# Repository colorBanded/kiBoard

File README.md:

# kiBoard
Full 104-key Keyboard designed as a submission for the **2026 Hackclub Stardance/Outpost Event**, created using KiCAD and Fusion 360. Uses the QMK firmware for ease of use and modularity.

## Features
* Raspberry Pi Pico based microcontroller
* 160 Keys
* Second function row + built in macro pad

## Layout

## Enclosure

-- I made the enclosure screwless so that you could nudge the top on for easier access to the internal board. (feel free to mess with it)

## BOM
| Reference | Qty | Value | Footprint | Datasheet |
|-----------|-----|-------|-----------|-----------|
| A1 | 1 | RaspberryPi_Pico | Module:RaspberryPi_Pico_Common_Unspecified | https://datasheets.raspberrypi.com/pico/pico-datasheet.pdf |
| D1–D158 | 158 | 1N4148 | Diode_THT:D_DO-35_SOD27_P7.62mm_Horizontal | https://assets.nexperia.com/documents/data-sheet/1N4148_1N4448.pdf |
| SW1–SW158 | 158 | SW_Push_45deg | Button_Switch_Keyboard:SW_Cherry_MX_1.00u_PCB | |
| SW159 | 1 | SW_Push | Button_Switch_Keyboard:SW_Cherry_MX_1.00u_PCB | |
| U1 | 1 | PCF8574AP | Package_DIP:DIP-16_W7.62mm | https://www.nxp.com/docs/en/data-sheet/PCF8574_PCF8574A.pdf |

Note: You can use any extended regular keyboard keycap set but it will need extra standard 1.0u keycaps for the remaining keys.

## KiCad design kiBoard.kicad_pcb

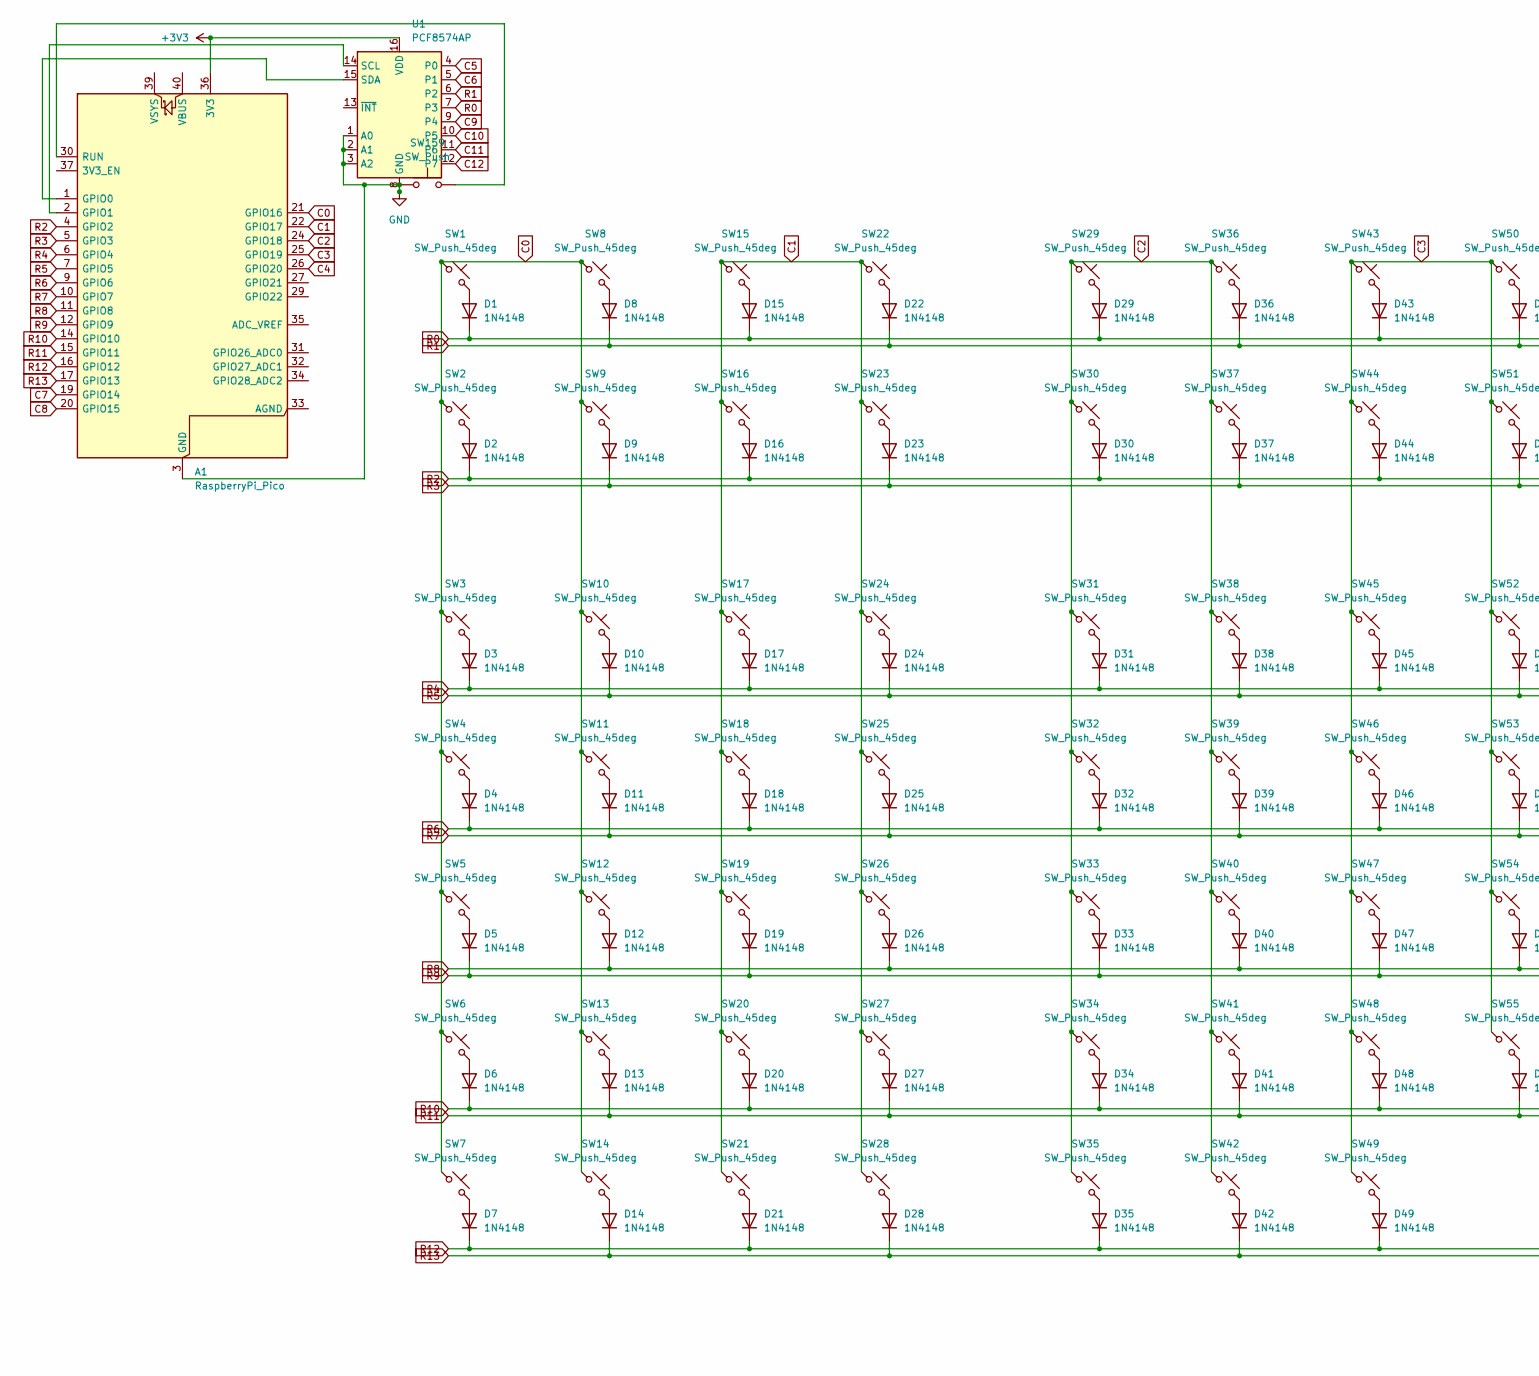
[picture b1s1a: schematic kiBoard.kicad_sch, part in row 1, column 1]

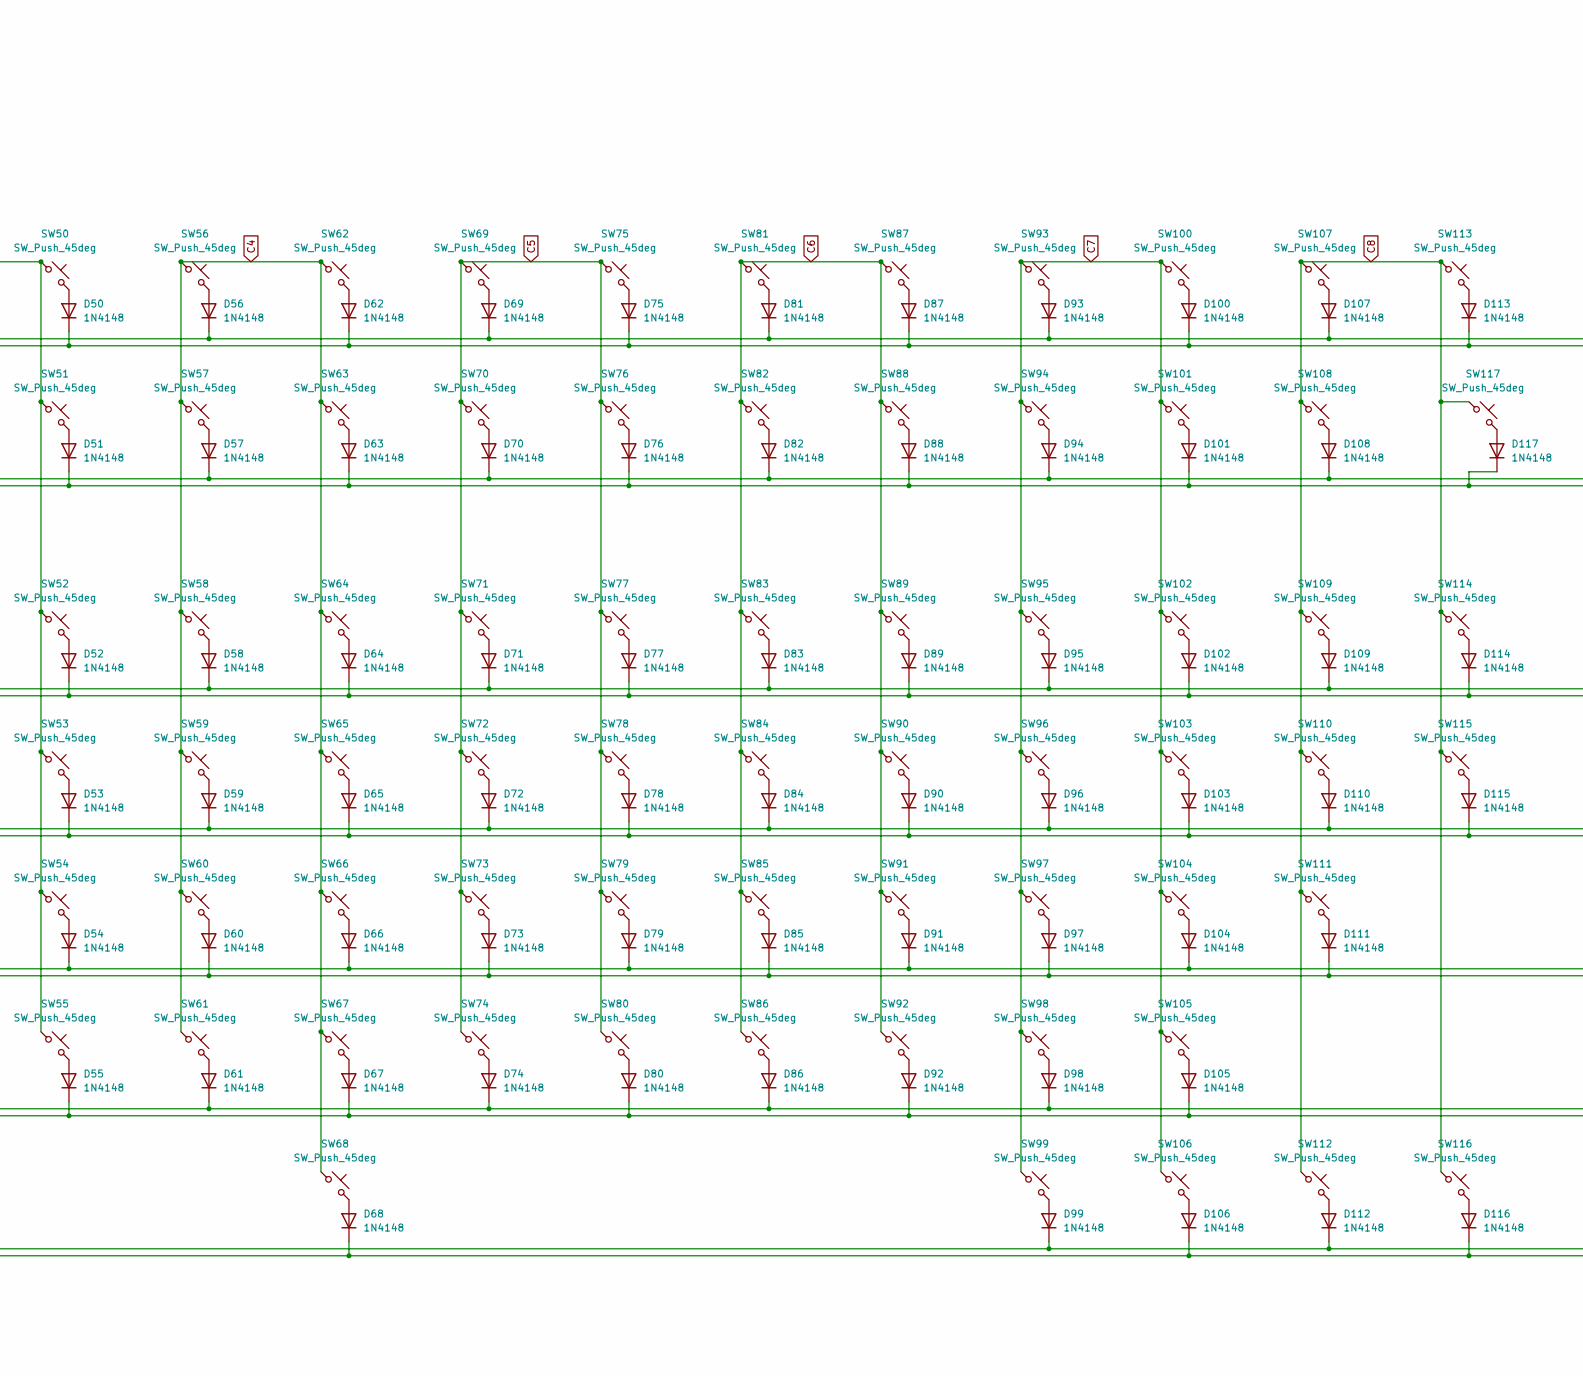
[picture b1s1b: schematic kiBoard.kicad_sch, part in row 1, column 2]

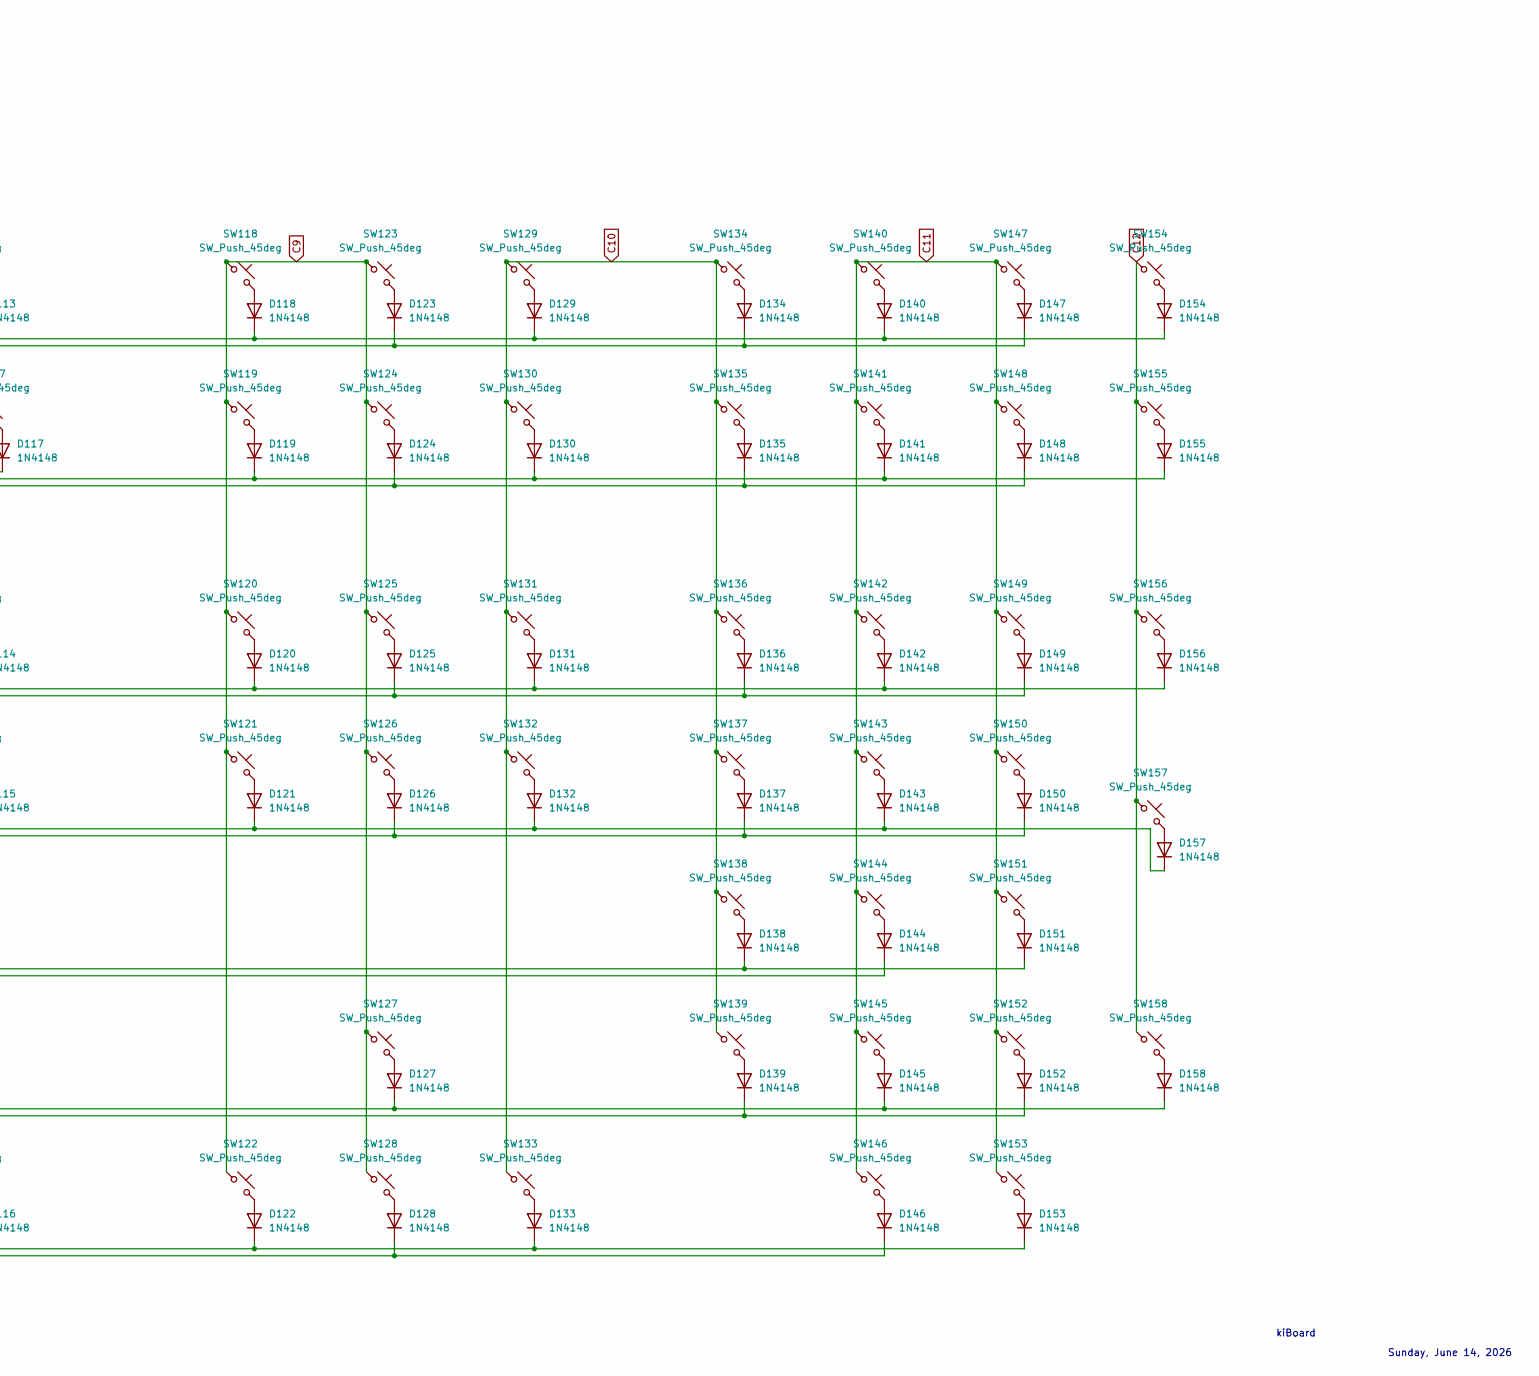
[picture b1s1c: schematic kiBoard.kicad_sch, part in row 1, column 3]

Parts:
A1: RaspberryPi_Pico; RaspberryPi_Pico_Common_Unspecified
D1, D2, D3, D4, D5, D6, D7, D8, D9, D10, D11, D12, D13, D14, D15, D16, D17, D18, D19, D20, D21, D22, D23, D24, D25, D26, D27, D28, D29, D30, D31, D32, D33, D34, D35, D36, D37, D38, D39, D40, D41, D42, D43, D44, D45, D46, D47, D48, D49, D50, D51, D52, D53, D54, D55, D56, D57, D58, D59, D60, D61, D62, D63, D64, D65, D66, D67, D68, D69, D70, D71, D72, D73, D74, D75, D76, D77, D78, D79, D80, D81, D82, D83, D84, D85, D86, D87, D88, D89, D90, D91, D92, D93, D94, D95, D96, D97, D98, D99, D100, D101, D102, D103, D104, D105, D106, D107, D108, D109, D110, D111, D112, D113, D114, D115, D116, D117, D118, D119, D120, D121, D122, D123, D124, D125, D126, D127, D128, D129, D130, D131, D132, D133, D134, D135, D136, D137, D138, D139, D140, D141, D142, D143, D144, D145, D146, D147, D148, D149, D150, D151, D152, D153, D154, D155, D156, D157, D158: 1N4148; D_DO-35_SOD27_P7.62mm_Horizontal
SW1, SW2, SW3, SW4, SW5, SW6, SW7, SW8, SW9, SW10, SW11, SW12, SW13, SW14, SW15, SW16, SW17, SW18, SW19, SW20, SW21, SW22, SW23, SW24, SW25, SW26, SW27, SW28, SW29, SW30, SW31, SW32, SW33, SW34, SW35, SW36, SW37, SW38, SW39, SW40, SW41, SW42, SW43, SW44, SW45, SW46, SW47, SW48, SW49, SW50, SW51, SW52, SW53, SW54, SW55, SW56, SW57, SW58, SW59, SW60, SW61, SW62, SW63, SW64, SW65, SW66, SW67, SW68, SW69, SW70, SW71, SW72, SW73, SW74, SW75, SW76, SW77, SW78, SW79, SW80, SW81, SW82, SW83, SW84, SW85, SW86, SW87, SW88, SW89, SW90, SW91, SW92, SW93, SW94, SW95, SW96, SW97, SW98, SW99, SW100, SW101, SW102, SW103, SW104, SW105, SW106, SW107, SW108, SW109, SW110, SW111, SW112, SW113, SW114, SW115, SW116, SW117, SW118, SW119, SW120, SW121, SW122, SW123, SW124, SW125, SW126, SW127, SW128, SW129, SW130, SW131, SW132, SW133, SW134, SW135, SW136, SW137, SW138, SW139, SW140, SW141, SW142, SW143, SW144, SW145, SW146, SW147, SW148, SW149, SW150, SW151, SW152, SW153, SW154, SW155, SW156, SW157, SW158: SW_Push_45deg; SW_Cherry_MX_1.00u_PCB
SW159: SW_Push; SW_Cherry_MX_1.00u_PCB
U1: PCF8574AP; DIP-16_W7.62mm

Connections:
+3V3: A1.36 (3V3), U1.16 (VDD)
C0: A1.21 (GPIO16), SW1.1, SW2.1, SW3.1, SW4.1, SW5.1, SW6.1, SW7.1, SW8.1, SW9.1, SW10.1, SW11.1, SW12.1, SW13.1, SW14.1
C1: A1.22 (GPIO17), SW15.1, SW16.1, SW17.1, SW18.1, SW19.1, SW20.1, SW21.1, SW22.1, SW23.1, SW24.1, SW25.1, SW26.1, SW27.1, SW28.1
C2: A1.24 (GPIO18), SW29.1, SW30.1, SW31.1, SW32.1, SW33.1, SW34.1, SW35.1, SW36.1, SW37.1, SW38.1, SW39.1, SW40.1, SW41.1, SW42.1
C3: A1.25 (GPIO19), SW43.1, SW44.1, SW45.1, SW46.1, SW47.1, SW48.1, SW49.1, SW50.1, SW51.1, SW52.1, SW53.1, SW54.1, SW55.1
C4: A1.26 (GPIO20), SW56.1, SW57.1, SW58.1, SW59.1, SW60.1, SW61.1, SW62.1, SW63.1, SW64.1, SW65.1, SW66.1, SW67.1, SW68.1
C5: SW69.1, SW70.1, SW71.1, SW72.1, SW73.1, SW74.1, SW75.1, SW76.1, SW77.1, SW78.1, SW79.1, SW80.1, U1.4 (P0)
C6: SW81.1, SW82.1, SW83.1, SW84.1, SW85.1, SW86.1, SW87.1, SW88.1, SW89.1, SW90.1, SW91.1, SW92.1, U1.5 (P1)
C7: A1.19 (GPIO14), SW93.1, SW94.1, SW95.1, SW96.1, SW97.1, SW98.1, SW99.1, SW100.1, SW101.1, SW102.1, SW103.1, SW104.1, SW105.1, SW106.1
C8: A1.20 (GPIO15), SW107.1, SW108.1, SW109.1, SW110.1, SW111.1, SW112.1, SW113.1, SW114.1, SW115.1, SW116.1, SW117.1
C9: SW118.1, SW119.1, SW120.1, SW121.1, SW122.1, SW123.1, SW124.1, SW125.1, SW126.1, SW127.1, SW128.1, U1.9 (P4)
C10: SW129.1, SW130.1, SW131.1, SW132.1, SW133.1, SW134.1, SW135.1, SW136.1, SW137.1, SW138.1, SW139.1, U1.10 (P5)
C11: SW140.1, SW141.1, SW142.1, SW143.1, SW144.1, SW145.1, SW146.1, SW147.1, SW148.1, SW149.1, SW150.1, SW151.1, SW152.1, SW153.1, U1.11 (P6)
C12: SW154.1, SW155.1, SW156.1, SW157.1, SW158.1, U1.12 (P7)
GND: A1.3 (GND), A1.8 (GND), A1.13 (GND), A1.18 (GND), A1.23 (GND), A1.28 (GND), A1.38 (GND), SW159.1, U1.1 (A0), U1.2 (A1), U1.3 (A2), U1.8 (GND)
unnamed: A1.1 (GPIO0), U1.15 (SDA)
unnamed: A1.2 (GPIO1), U1.14 (SCL)
unnamed: A1.30 (RUN), SW159.2
unnamed: D1.2 (A), SW1.2
unnamed: D2.2 (A), SW2.2
unnamed: D3.2 (A), SW3.2
unnamed: D4.2 (A), SW4.2
unnamed: D5.2 (A), SW5.2
unnamed: D6.2 (A), SW6.2
unnamed: D7.2 (A), SW7.2
unnamed: D8.2 (A), SW8.2
unnamed: D9.2 (A), SW9.2
unnamed: D10.2 (A), SW10.2
unnamed: D11.2 (A), SW11.2
unnamed: D12.2 (A), SW12.2
unnamed: D13.2 (A), SW13.2
unnamed: D14.2 (A), SW14.2
unnamed: D15.2 (A), SW15.2
unnamed: D16.2 (A), SW16.2
unnamed: D17.2 (A), SW17.2
unnamed: D18.2 (A), SW18.2
unnamed: D19.2 (A), SW19.2
unnamed: D20.2 (A), SW20.2
unnamed: D21.2 (A), SW21.2
unnamed: D22.2 (A), SW22.2
unnamed: D23.2 (A), SW23.2
unnamed: D24.2 (A), SW24.2
unnamed: D25.2 (A), SW25.2
unnamed: D26.2 (A), SW26.2
unnamed: D27.2 (A), SW27.2
unnamed: D28.2 (A), SW28.2
unnamed: D29.2 (A), SW29.2
unnamed: D30.2 (A), SW30.2
unnamed: D31.2 (A), SW31.2
unnamed: D32.2 (A), SW32.2
unnamed: D33.2 (A), SW33.2
unnamed: D34.2 (A), SW34.2
unnamed: D35.2 (A), SW35.2
unnamed: D36.2 (A), SW36.2
unnamed: D37.2 (A), SW37.2
unnamed: D38.2 (A), SW38.2
unnamed: D39.2 (A), SW39.2
unnamed: D40.2 (A), SW40.2
unnamed: D41.2 (A), SW41.2
unnamed: D42.2 (A), SW42.2
unnamed: D43.2 (A), SW43.2
unnamed: D44.2 (A), SW44.2
unnamed: D45.2 (A), SW45.2
unnamed: D46.2 (A), SW46.2
unnamed: D47.2 (A), SW47.2
unnamed: D48.2 (A), SW48.2
unnamed: D49.2 (A), SW49.2
unnamed: D50.2 (A), SW50.2
unnamed: D51.2 (A), SW51.2
unnamed: D52.2 (A), SW52.2
unnamed: D53.2 (A), SW53.2
unnamed: D54.2 (A), SW54.2
unnamed: D55.2 (A), SW55.2
unnamed: D56.2 (A), SW56.2
unnamed: D57.2 (A), SW57.2
unnamed: D58.2 (A), SW58.2
unnamed: D59.2 (A), SW59.2
unnamed: D60.2 (A), SW60.2
unnamed: D61.2 (A), SW61.2
unnamed: D62.2 (A), SW62.2
unnamed: D63.2 (A), SW63.2
unnamed: D64.2 (A), SW64.2
unnamed: D65.2 (A), SW65.2
unnamed: D66.2 (A), SW66.2
unnamed: D67.2 (A), SW67.2
unnamed: D68.2 (A), SW68.2
unnamed: D69.2 (A), SW69.2
unnamed: D70.2 (A), SW70.2
unnamed: D71.2 (A), SW71.2
unnamed: D72.2 (A), SW72.2
unnamed: D73.2 (A), SW73.2
unnamed: D74.2 (A), SW74.2
unnamed: D75.2 (A), SW75.2
unnamed: D76.2 (A), SW76.2
unnamed: D77.2 (A), SW77.2
unnamed: D78.2 (A), SW78.2
unnamed: D79.2 (A), SW79.2
unnamed: D80.2 (A), SW80.2
unnamed: D81.2 (A), SW81.2
unnamed: D82.2 (A), SW82.2
unnamed: D83.2 (A), SW83.2
unnamed: D84.2 (A), SW84.2
unnamed: D85.2 (A), SW85.2
unnamed: D86.2 (A), SW86.2
unnamed: D87.2 (A), SW87.2
unnamed: D88.2 (A), SW88.2
unnamed: D89.2 (A), SW89.2
unnamed: D90.2 (A), SW90.2
unnamed: D91.2 (A), SW91.2
unnamed: D92.2 (A), SW92.2
unnamed: D93.2 (A), SW93.2
unnamed: D94.2 (A), SW94.2
unnamed: D95.2 (A), SW95.2
unnamed: D96.2 (A), SW96.2
unnamed: D97.2 (A), SW97.2
unnamed: D98.2 (A), SW98.2
unnamed: D99.2 (A), SW99.2
unnamed: D100.2 (A), SW100.2
unnamed: D101.2 (A), SW101.2
unnamed: D102.2 (A), SW102.2
unnamed: D103.2 (A), SW103.2
unnamed: D104.2 (A), SW104.2
unnamed: D105.2 (A), SW105.2
unnamed: D106.2 (A), SW106.2
unnamed: D107.2 (A), SW107.2
unnamed: D108.2 (A), SW108.2
unnamed: D109.2 (A), SW109.2
unnamed: D110.2 (A), SW110.2
unnamed: D111.2 (A), SW111.2
unnamed: D112.2 (A), SW112.2
unnamed: D113.2 (A), SW113.2
unnamed: D114.2 (A), SW114.2
unnamed: D115.2 (A), SW115.2
unnamed: D116.2 (A), SW116.2
unnamed: D117.2 (A), SW117.2
unnamed: D118.2 (A), SW118.2
unnamed: D119.2 (A), SW119.2
unnamed: D120.2 (A), SW120.2
unnamed: D121.2 (A), SW121.2
unnamed: D122.2 (A), SW122.2
unnamed: D123.2 (A), SW123.2
unnamed: D124.2 (A), SW124.2
unnamed: D125.2 (A), SW125.2
unnamed: D126.2 (A), SW126.2
unnamed: D127.2 (A), SW127.2
unnamed: D128.2 (A), SW128.2
unnamed: D129.2 (A), SW129.2
unnamed: D130.2 (A), SW130.2
unnamed: D131.2 (A), SW131.2
unnamed: D132.2 (A), SW132.2
unnamed: D133.2 (A), SW133.2
unnamed: D134.2 (A), SW134.2
unnamed: D135.2 (A), SW135.2
unnamed: D136.2 (A), SW136.2
unnamed: D137.2 (A), SW137.2
unnamed: D138.2 (A), SW138.2
unnamed: D139.2 (A), SW139.2
unnamed: D140.2 (A), SW140.2
unnamed: D141.2 (A), SW141.2
unnamed: D142.2 (A), SW142.2
unnamed: D143.2 (A), SW143.2
unnamed: D144.2 (A), SW144.2
unnamed: D145.2 (A), SW145.2
unnamed: D146.2 (A), SW146.2
unnamed: D147.2 (A), SW147.2
unnamed: D148.2 (A), SW148.2
unnamed: D149.2 (A), SW149.2
unnamed: D150.2 (A), SW150.2
unnamed: D151.2 (A), SW151.2
unnamed: D152.2 (A), SW152.2
unnamed: D153.2 (A), SW153.2
unnamed: D154.2 (A), SW154.2
unnamed: D155.2 (A), SW155.2
unnamed: D156.2 (A), SW156.2
unnamed: D157.2 (A), SW157.2
unnamed: D158.2 (A), SW158.2
R0: D1.1 (K), D15.1 (K), D29.1 (K), D43.1 (K), D56.1 (K), D69.1 (K), D81.1 (K), D93.1 (K), D107.1 (K), D118.1 (K), D129.1 (K), D140.1 (K), D154.1 (K), U1.7 (P3)
R1: D8.1 (K), D22.1 (K), D36.1 (K), D50.1 (K), D62.1 (K), D75.1 (K), D87.1 (K), D100.1 (K), D113.1 (K), D123.1 (K), D134.1 (K), D147.1 (K), U1.6 (P2)
R2: A1.4 (GPIO2), D2.1 (K), D16.1 (K), D30.1 (K), D44.1 (K), D57.1 (K), D70.1 (K), D82.1 (K), D94.1 (K), D108.1 (K), D119.1 (K), D130.1 (K), D141.1 (K), D155.1 (K)
R3: A1.5 (GPIO3), D9.1 (K), D23.1 (K), D37.1 (K), D51.1 (K), D63.1 (K), D76.1 (K), D88.1 (K), D101.1 (K), D117.1 (K), D124.1 (K), D135.1 (K), D148.1 (K)
R4: A1.6 (GPIO4), D3.1 (K), D17.1 (K), D31.1 (K), D45.1 (K), D58.1 (K), D71.1 (K), D83.1 (K), D95.1 (K), D109.1 (K), D120.1 (K), D131.1 (K), D142.1 (K), D156.1 (K)
R5: A1.7 (GPIO5), D10.1 (K), D24.1 (K), D38.1 (K), D52.1 (K), D64.1 (K), D77.1 (K), D89.1 (K), D102.1 (K), D114.1 (K), D125.1 (K), D136.1 (K), D149.1 (K)
R6: A1.9 (GPIO6), D4.1 (K), D18.1 (K), D32.1 (K), D46.1 (K), D59.1 (K), D72.1 (K), D84.1 (K), D96.1 (K), D110.1 (K), D121.1 (K), D132.1 (K), D143.1 (K), D157.1 (K)
R7: A1.10 (GPIO7), D11.1 (K), D25.1 (K), D39.1 (K), D53.1 (K), D65.1 (K), D78.1 (K), D90.1 (K), D103.1 (K), D115.1 (K), D126.1 (K), D137.1 (K), D150.1 (K)
R8: A1.11 (GPIO8), D12.1 (K), D26.1 (K), D40.1 (K), D54.1 (K), D66.1 (K), D79.1 (K), D91.1 (K), D104.1 (K), D138.1 (K), D151.1 (K)
R9: A1.12 (GPIO9), D5.1 (K), D19.1 (K), D33.1 (K), D47.1 (K), D60.1 (K), D73.1 (K), D85.1 (K), D97.1 (K), D111.1 (K), D144.1 (K)
R10: A1.14 (GPIO10), D6.1 (K), D20.1 (K), D34.1 (K), D48.1 (K), D61.1 (K), D74.1 (K), D86.1 (K), D98.1 (K), D127.1 (K), D145.1 (K), D158.1 (K)
R11: A1.15 (GPIO11), D13.1 (K), D27.1 (K), D41.1 (K), D55.1 (K), D67.1 (K), D80.1 (K), D92.1 (K), D105.1 (K), D139.1 (K), D152.1 (K)
R12: A1.16 (GPIO12), D7.1 (K), D21.1 (K), D35.1 (K), D49.1 (K), D99.1 (K), D112.1 (K), D122.1 (K), D133.1 (K), D153.1 (K)
R13: A1.17 (GPIO13), D14.1 (K), D28.1 (K), D42.1 (K), D68.1 (K), D106.1 (K), D116.1 (K), D128.1 (K), D146.1 (K)

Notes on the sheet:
Sunday, June 14, 2026
kiBoard

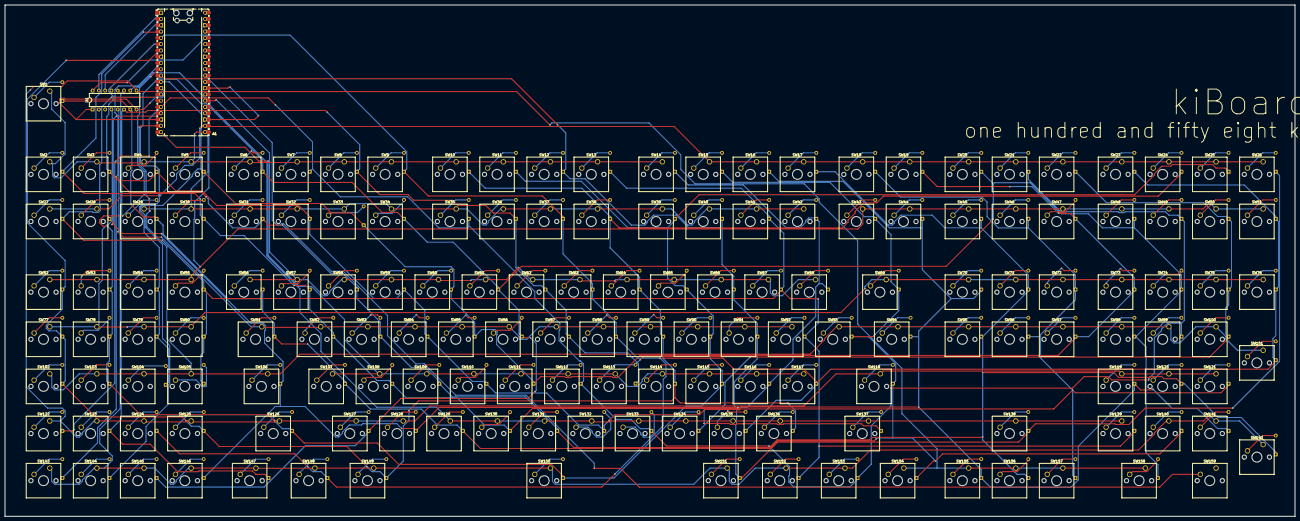
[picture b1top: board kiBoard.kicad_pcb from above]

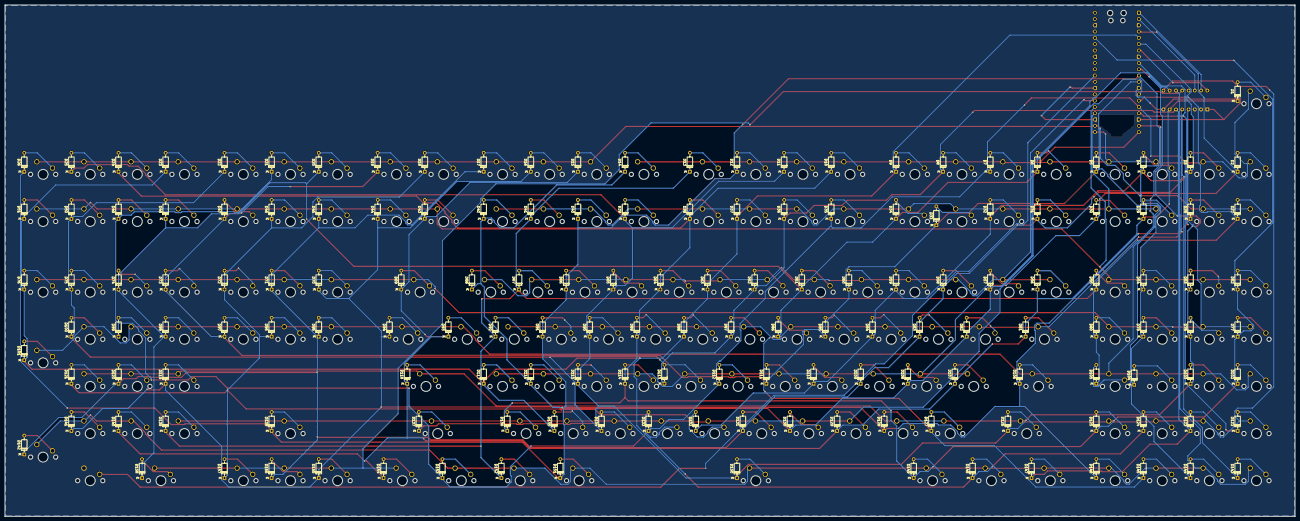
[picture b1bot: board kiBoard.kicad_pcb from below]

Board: 2 copper layers, 521.5 x 206.7 mm, 319 parts (158 on the bottom side), 190 nets.

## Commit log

2026-06-12 Update .gitignore
    MacOS garbage
2026-06-18 Updated Mainboard and finalized design
    I did everything in like one or two sittings so the dev logs gonna be hella long
2026-06-20 Reorganize Repository, added Gerbers and CAD Case model.
2026-06-20 Update README.md BOM
2026-06-20 Update README.md Notice
